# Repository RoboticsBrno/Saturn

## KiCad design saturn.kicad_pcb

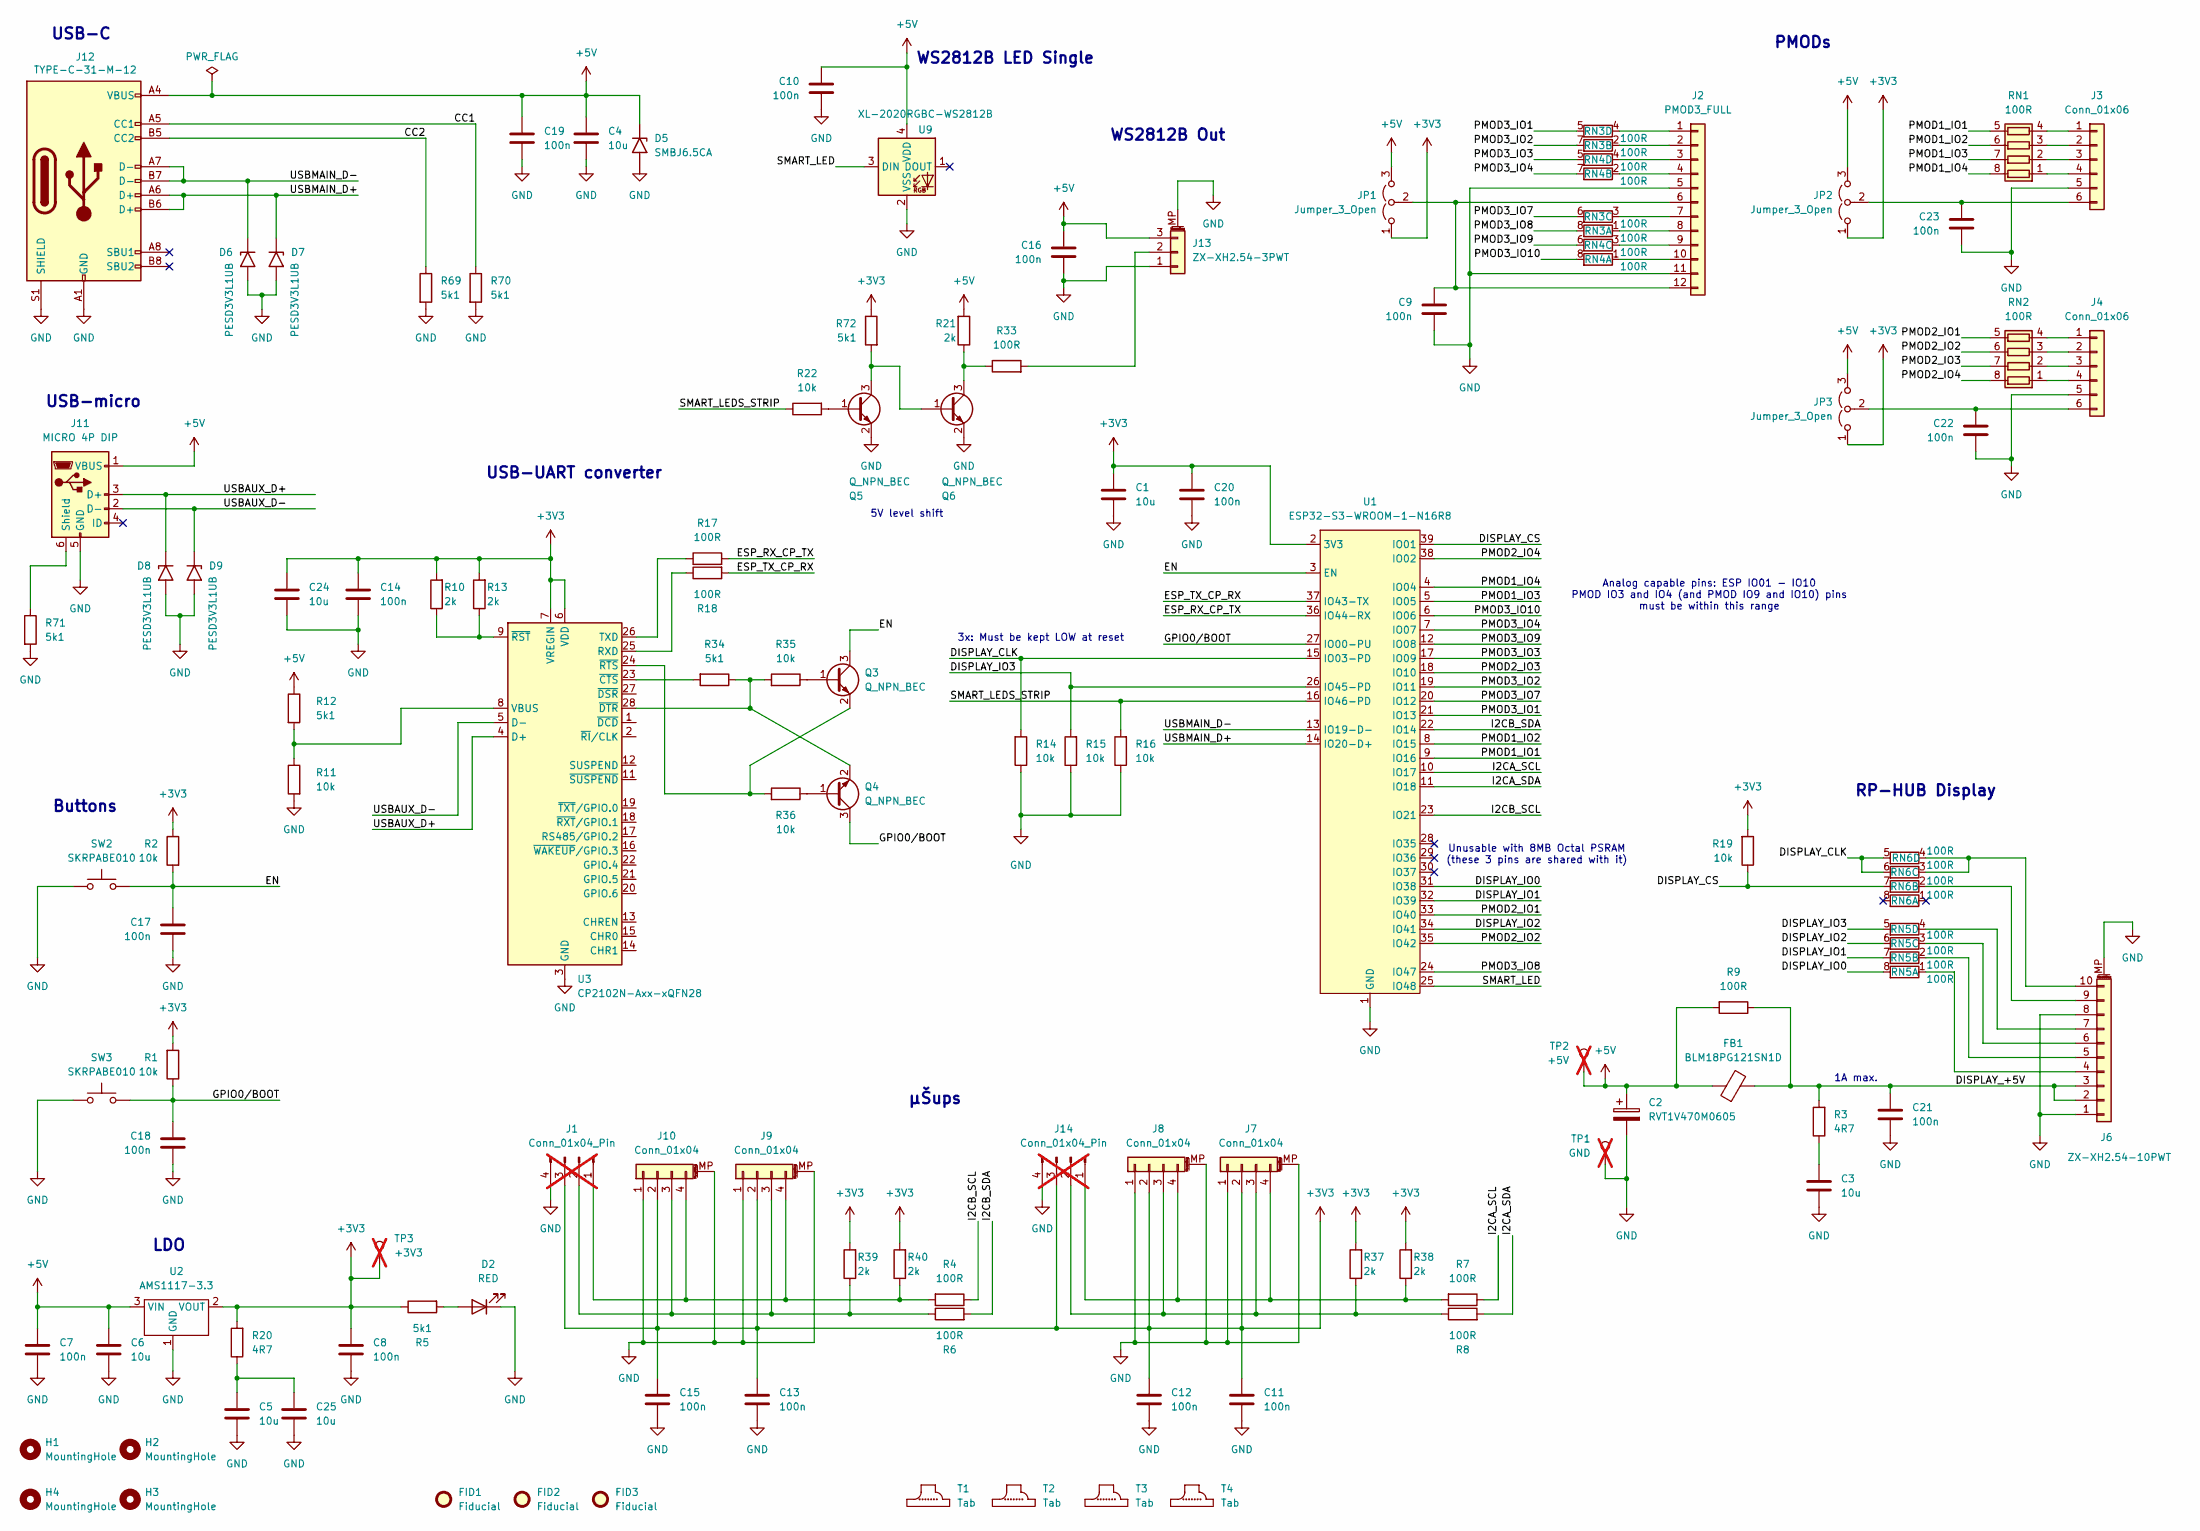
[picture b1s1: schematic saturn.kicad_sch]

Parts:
C1, C3, C4, C5, C6, C24, C25: 10u; C_0805_2012Metric; LCSC C15850
C2: RVT1V470M0605; CP_Elec_6.3x5.4; LCSC C72522
C7, C8, C9, C10, C11, C12, C13, C14, C15, C16, C17, C18, C19, C20, C21, C22, C23: 100n; C_0402_1005Metric; LCSC C307331
D2: RED; LED_0603_1608Metric; LCSC C965799
D5: SMBJ6.5CA; D_SMB; LCSC C7420377
D6, D7, D8, D9: PESD3V3L1UB; D_SOD-523; LCSC C3001945
FB1: BLM18PG121SN1D; L_0603_1608Metric; LCSC C14709
FID1, FID2, FID3: Fiducial; Fiducial_1mm_Mask2mm
H1, H2, H3, H4: MountingHole; MountingHole_3.2mm_M3_DIN965
J1, J14: Conn_01x04_Pin; PinSocket_1x04_P2.54mm_Vertical; not fitted
J2: PMOD3_FULL; PinSocket_PMOD_full; LCSC C2897426
J3, J4: Conn_01x06; PinSocket_PMOD_Half; LCSC C2897388
J6: ZX-XH2.54-10PWT; JST-XH-SMD-10Pin; LCSC C7429679
J7, J8, J9, J10: Conn_01x04; JST_SH_SM04B-SRSS-TB_1x04-1MP_P1.00mm_Horizontal; LCSC C7430446
J11: MICRO 4P DIP; USB_MICRO 4P DIP; LCSC C456008
J12: TYPE-C-31-M-12; USB_C_Receptacle_HRO_TYPE-C-31-M-12_With_THR_Paste; LCSC C165948
J13: ZX-XH2.54-3PWT; JST-XH-SMD-3Pin; LCSC C7429672
JP1, JP2, JP3: Jumper_3_Open; PinHeader_1x03_P2.54mm_Vertical_SMD_Pin1Left_LargePads; LCSC C41417360
Q3, Q4, Q5, Q6: Q_NPN_BEC; SOT-23; LCSC C20526
R1, R2, R11, R14, R15, R16, R19, R22, R35, R36: 10k; R_0402_1005Metric; LCSC C25744
R3, R20: 4R7; R_0805_2012Metric; LCSC C17675
R4, R6, R7, R8, R9, R17, R18, R33: 100R; R_0402_1005Metric; LCSC C25076
R5, R12, R34, R69, R70, R71, R72: 5k1; R_0402_1005Metric; LCSC C25905
R10, R13, R21, R37, R38, R39, R40: 2k; R_0402_1005Metric; LCSC C4109
RN1, RN2, RN3, RN4, RN5, RN6: 100R; R_Array_Convex_4x0603; LCSC C25506
SW2, SW3: SKRPABE010; SW_SMD_LargePads; LCSC C115360
T1, T2, T3, T4: Tab
TP1: GND; PinHeader_1x01_P2.54mm_Vertical; not fitted
TP2: +5V; PinHeader_1x01_P2.54mm_Vertical; not fitted
TP3: +3V3; PinHeader_1x01_P2.54mm_Vertical; not fitted
U1: ESP32-S3-WROOM-1-N16R8; ESP32-S3-WROOM; LCSC C2913202
U2: AMS1117-3.3; SOT-223-3_TabPin2; LCSC C6186
U3: CP2102N-Axx-xQFN28; QFN-28-1EP_5x5mm_P0.5mm_EP3.35x3.35mm; LCSC C964632
U9: XL-2020RGBC-WS2812B; LED_WS2812B-2020_PLCC4_2.0x2.0mm; LCSC C5349955

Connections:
+3V3: C1.1, C8.1, C11.1, C12.1, C13.1, C14.1, C15.1, C20.1, C24.1, J1.3, J7.2, J8.2, J9.2, J10.2, J14.3, JP1.1 (A), JP2.1 (A), JP3.1 (A), R1.2, R2.1, R5.1, R10.2, R13.2, R19.2, R20.2, R37.2, R38.2, R39.2, R40.2, R72.1, TP3.1 (1_1), U1.2 (3V3), U2.2 (VOUT), U3.6 (VDD), U3.7 (VREGIN)
+5V: C2.1, C4.1, C6.1, C7.1, C10.1, C16.1, C19.1, D5.1 (A1), FB1.1, J11.1 (VBUS), J12.A4 (VBUS), J12.A9 (VBUS), J12.B4 (VBUS), J12.B9 (VBUS), J13.3, JP1.3 (B), JP2.3 (B), JP3.3 (B), R9.2, R12.1, R21.2, TP2.1 (1_1), U2.3 (VIN), U9.4 (VDD)
/CC1: J12.A5 (CC1), R70.1
/CC2: J12.B5 (CC2), R69.1
/DISPLAY_+5V: C21.1, FB1.2, J6.2, J6.3, R3.2, R9.1
/DISPLAY_CLK: R14.2, RN6.5 (R4.2), RN6.6 (R3.2), U1.15 (IO03-PD)
/DISPLAY_CS: R19.1, RN6.7 (R2.2), U1.39 (IO01)
/DISPLAY_IO0: RN5.8 (R1.2), U1.31 (IO38)
/DISPLAY_IO1: RN5.7 (R2.2), U1.32 (IO39)
/DISPLAY_IO2: RN5.6 (R3.2), U1.34 (IO41)
/DISPLAY_IO3: R15.2, RN5.5 (R4.2), U1.26 (IO45-PD)
/EN: C17.1, Q3.3 (C), R2.2, SW2.1, U1.3 (EN)
/ESP_RX_CP_TX: R17.2, U1.36 (IO44-RX)
/ESP_TX_CP_RX: R18.2, U1.37 (IO43-TX)
/GPIO0/BOOT: C18.1, Q4.3 (C), R1.1, SW3.1, U1.27 (IO00-PU)
/I2CA_SCL: R7.1, U1.10 (IO17)
/I2CA_SDA: R8.2, U1.11 (IO18)
/I2CB_SCL: R4.1, U1.23 (IO21)
/I2CB_SDA: R6.2, U1.22 (IO14)
/PMOD1_IO1: RN1.5 (R4.2), U1.9 (IO16)
/PMOD1_IO2: RN1.6 (R3.2), U1.8 (IO15)
/PMOD1_IO3: RN1.7 (R2.2), U1.5 (IO05)
/PMOD1_IO4: RN1.8 (R1.2), U1.4 (IO04)
/PMOD2_IO1: RN2.5 (R4.2), U1.33 (IO40)
/PMOD2_IO2: RN2.6 (R3.2), U1.35 (IO42)
/PMOD2_IO3: RN2.7 (R2.2), U1.18 (IO10)
/PMOD2_IO4: RN2.8 (R1.2), U1.38 (IO02)
/PMOD3_IO1: RN3.5 (R4.2), U1.21 (IO13)
/PMOD3_IO2: RN3.7 (R2.2), U1.19 (IO11)
/PMOD3_IO3: RN4.5 (R4.2), U1.17 (IO09)
/PMOD3_IO4: RN4.7 (R2.2), U1.7 (IO07)
/PMOD3_IO7: RN3.6 (R3.2), U1.20 (IO12)
/PMOD3_IO8: RN3.8 (R1.2), U1.24 (IO47)
/PMOD3_IO9: RN4.6 (R3.2), U1.12 (IO08)
/PMOD3_IO10: RN4.8 (R1.2), U1.6 (IO06)
/SMART_LED: U1.25 (IO48), U9.3 (DIN)
/SMART_LEDS_STRIP: R16.2, R22.1, U1.16 (IO46-PD)
/USBAUX_D+: D8.1 (A1), J11.3 (D+), U3.4 (D+)
/USBAUX_D-: D9.1 (A1), J11.2 (D-), U3.5 (D-)
/USBMAIN_D+: D7.1 (A1), J12.A6 (D+), J12.B6 (D+), U1.14 (IO20-D+)
/USBMAIN_D-: D6.1 (A1), J12.A7 (D-), J12.B7 (D-), U1.13 (IO19-D-)
GND: C1.2, C2.2, C3.2, C4.2, C5.2, C6.2, C7.2, C8.2, C9.2, C10.2, C11.2, C12.2, C13.2, C14.2, C15.2, C16.2, C17.2, C18.2, C19.2, C20.2, C21.2, C22.2, C23.2, C24.2, C25.2, D2.1 (K), D5.2 (A2), D6.2 (A2), D7.2 (A2), D8.2 (A2), D9.2 (A2), J1.4, J2.5, J2.11, J3.5, J4.5, J6.1, J6.8, J6.MP (MountPin), J7.1, J7.MP (MountPin), J8.1, J8.MP (MountPin), J9.1, J9.MP (MountPin), J10.1, J10.MP (MountPin), J11.5 (GND), J12.A1 (GND), J12.A12 (GND), J12.B1 (GND), J12.B12 (GND), J12.S1 (SHIELD), J13.1, J13.MP (MountPin), J14.4, Q5.2 (E), Q6.2 (E), R11.2, R14.1, R15.1, R16.1, R69.2, R70.2, R71.2, SW2.2, SW3.2, TP1.1 (1_1), U1.1 (GND), U1.40 (GND), U1.41 (GND), U2.1 (GND), U3.3 (GND), U3.29 (GND), U9.2 (VSS)
unnamed: C3.1, R3.1
unnamed: C5.1, C25.1, R20.1
unnamed: D2.2 (A), R5.2
unnamed: J1.1, J9.4, J10.4, R4.2, R40.1
unnamed: J1.2, J9.3, J10.3, R6.1, R39.1
unnamed: J2.1, RN3.4 (R4.1)
unnamed: J2.2, RN3.2 (R2.1)
unnamed: J2.3, RN4.4 (R4.1)
unnamed: J2.4, RN4.2 (R2.1)
unnamed: J2.7, RN3.3 (R3.1)
unnamed: J2.8, RN3.1 (R1.1)
unnamed: J2.9, RN4.3 (R3.1)
unnamed: J2.10, RN4.1 (R1.1)
unnamed: C9.1, J2.6, J2.12, JP1.2 (C)
unnamed: J3.1, RN1.4 (R4.1)
unnamed: J3.2, RN1.3 (R3.1)
unnamed: J3.3, RN1.2 (R2.1)
unnamed: J3.4, RN1.1 (R1.1)
unnamed: C23.1, J3.6, JP2.2 (C)
unnamed: J4.1, RN2.4 (R4.1)
unnamed: J4.2, RN2.3 (R3.1)
unnamed: J4.3, RN2.2 (R2.1)
unnamed: J4.4, RN2.1 (R1.1)
unnamed: C22.1, J4.6, JP3.2 (C)
unnamed: J6.4, RN5.1 (R1.1)
unnamed: J6.5, RN5.2 (R2.1)
unnamed: J6.6, RN5.3 (R3.1)
unnamed: J6.7, RN5.4 (R4.1)
unnamed: J6.9, RN6.2 (R2.1)
unnamed: J6.10, RN6.3 (R3.1), RN6.4 (R4.1)
unnamed: J11.6 (Shield), R71.1
unnamed: J13.2, R33.2
unnamed: J7.4, J8.4, J14.1, R7.2, R38.1
unnamed: J7.3, J8.3, J14.2, R8.1, R37.1
unnamed: Q3.1 (B), R35.1
unnamed: Q3.2 (E), R36.2, U3.24 (~RTS)
unnamed: Q4.1 (B), R36.1
unnamed: Q4.2 (E), R34.1, R35.2, U3.28 (~DTR)
unnamed: Q5.1 (B), R22.2
unnamed: Q5.3 (C), Q6.1 (B), R72.2
unnamed: Q6.3 (C), R21.1, R33.1
unnamed: R18.1, U3.25 (RXD)
unnamed: R17.1, U3.26 (TXD)
unnamed: R11.1, R12.2, U3.8 (VBUS)
unnamed: R34.2, U3.23 (~CTS)
unnamed: R10.1, R13.1, U3.9 (~RST)

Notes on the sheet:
USB-UART converter
Unusable with 8MB Octal PSRAM (these 3 pins are shared with it)
WS2812B LED Single
3x: Must be kept LOW at reset
1A max.
RP-HUB Display
µŠups
PMODs
USB-micro
WS2812B Out
USB-C
LDO
5V level shift
Buttons
Analog capable pins: ESP IO01 - IO10 PMOD IO3 and IO4 (and PMOD IO9 and IO10) pins must be within this range

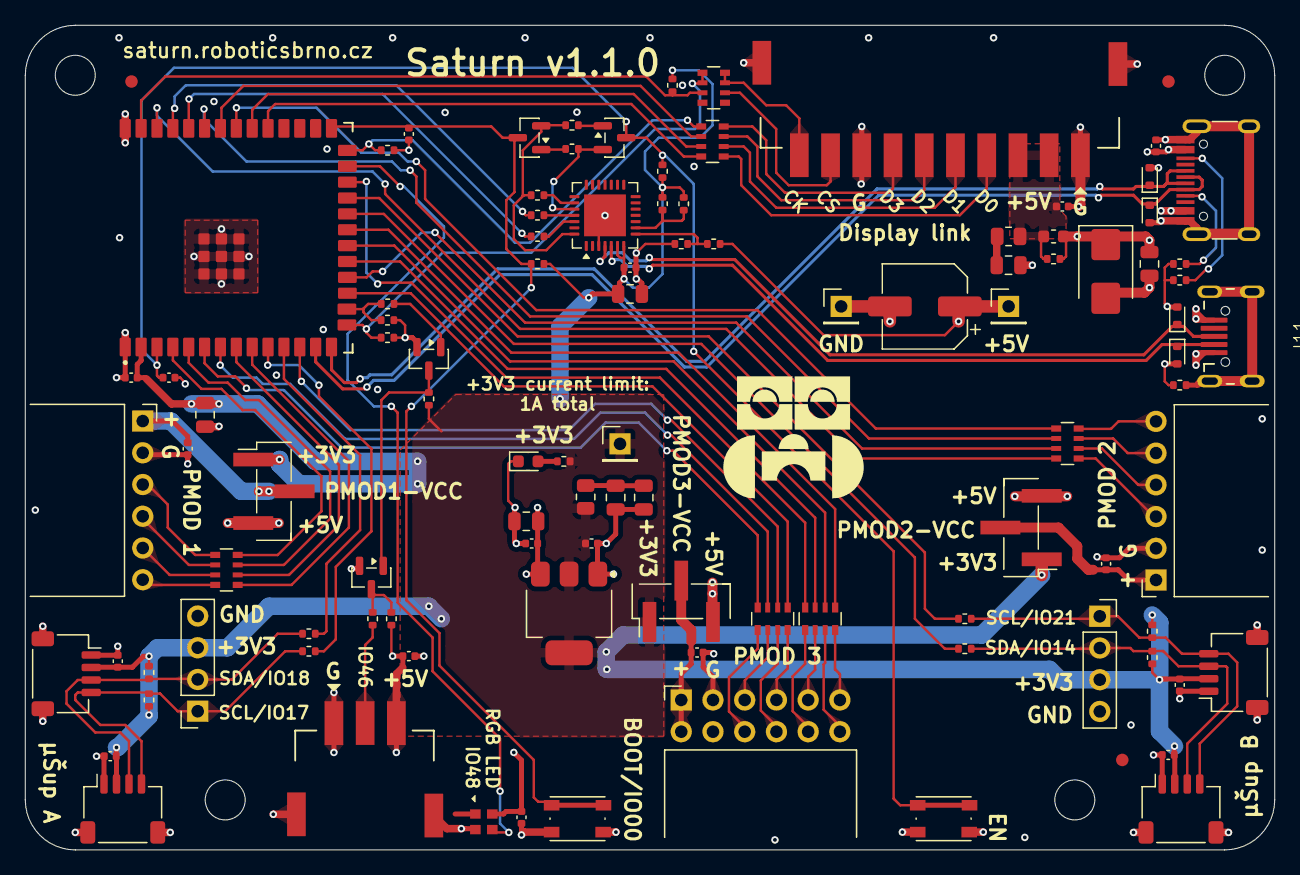
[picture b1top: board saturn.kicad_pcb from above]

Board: 4 copper layers, 100.0 x 66.0 mm, 112 parts (0 on the bottom side), 88 nets.

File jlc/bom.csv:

Comment,Designator,Footprint,LCSC
100R,"R4,R6,R7,R8,R9,R17,R18,R33",Resistor_SMD:R_0402_1005Metric,C25076
ZX-XH2.54-3PWT,J13,JST-XH-SMT:JST-XH-SMD-3Pin,C7429672
2k,"R10,R13,R21,R37,R38,R39,R40",Resistor_SMD:R_0402_1005Metric,C4109
Jumper_3_Open,"JP1,JP2,JP3",PinHeader_jumper:PinHeader_1x03_P2.54mm_Vertical_SMD_Pin1Left_LargePads,C41417360
5k1,"R5,R12,R34,R69,R70,R71,R72",Resistor_SMD:R_0402_1005Metric,C25905
10k,"R1,R2,R11,R14,R15,R16,R19,R22,R35,R36",Resistor_SMD:R_0402_1005Metric,C25744
100n,"C7,C8,C9,C10,C11,C12,C13,C14,C15,C16,C17,C18,C19,C20,C21,C22,C23",Capacitor_SMD:C_0402_1005Metric,C307331
100R,"RN1,RN2,RN3,RN4,RN5,RN6",Resistor_SMD:R_Array_Convex_4x0603,C25506
10u,"C1,C3,C4,C5,C6,C24,C25",Capacitor_SMD:C_0805_2012Metric,C15850
MICRO 4P DIP,J11,USB_Conn:USB_MICRO 4P DIP,C456008
Q_NPN_BEC,"Q3,Q4,Q5,Q6",Package_TO_SOT_SMD:SOT-23,C20526
4R7,"R3,R20",Resistor_SMD:R_0805_2012Metric,C17675
SMBJ6.5CA,D5,Diode_SMD:D_SMB,C7420377
Conn_01x04,"J7,J8,J9,J10",Connector_JST:JST_SH_SM04B-SRSS-TB_1x04-1MP_P1.00mm_Horizontal,C7430446
SKRPABE010,"SW2,SW3",Switch_SMT:SW_SMD_LargePads,C115360
PESD3V3L1UB,"D6,D7,D8,D9",Diode_SMD:D_SOD-523,C3001945
RED,D2,LED_SMD:LED_0603_1608Metric,C965799
BLM18PG121SN1D,FB1,Inductor_SMD:L_0603_1608Metric,C14709
XL-2020RGBC-WS2812B,U9,XL-2020RGBC-WS2812B:LED_WS2812B-2020_PLCC4_2.0x2.0mm,C5349955
ZX-XH2.54-10PWT,J6,JST-XH-SMT:JST-XH-SMD-10Pin,C7429679
CP2102N-Axx-xQFN28,U3,Package_DFN_QFN:QFN-28-1EP_5x5mm_P0.5mm_EP3.35x3.35mm,C964632
ESP32-S3-WROOM-1-N16R8,U1,ESP32-WROOM:ESP32-S3-WROOM,C2913202
AMS1117-3.3,U2,Package_TO_SOT_SMD:SOT-223-3_TabPin2,C6186
Conn_01x06,"J3,J4",PinSocket_PMOD:PinSocket_PMOD_Half,C2897388
TYPE-C-31-M-12,J12,USB_Conn:USB_C_Receptacle_HRO_TYPE-C-31-M-12_With_THR_Paste,C165948
PMOD3_FULL,J2,PinSocket_PMOD:PinSocket_PMOD_full,C2897426
RVT1V470M0605,C2,Capacitor_SMD:CP_Elec_6.3x5.4,C72522

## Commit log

2026-02-27 Add hw review 2nd version
2026-03-03 Release v1.0.0
2026-04-11 Switch to Kicad 10
2026-04-23 Fix PMOD ADC pin assignment, tune silkscreen
2026-04-25 Add PMOD polarity mark on Top
2026-04-25 Fix 5V unroute
2026-04-25 Use unipolar TVS diodes, tune switch values
2026-04-25 Use SMT PMOD jumper header
2026-04-25 Use SMT JST-XH connectors
2026-04-25 Remove unneeded JST XH files
2026-04-25 Add CHANGELOG.md
2026-04-25 Tune silkscreen
2026-05-10 Tune silkscreen, enlarge SMT switch pads
2026-05-10 Add project-specific ESP32, USB, WS2812B footprints
2026-05-10 Add enlarge-pad switch footprint
2026-05-10 Add fp-lib-table
2026-05-10 Add fubar Button 3D model
2026-05-13 Use 0805 10u capacitors (cheaper)
2026-05-13 Use AMS1117-3.3 LDO (cheaper)
2026-05-13 Add LDO output cap series resistance
2026-05-16 Separate LED Strip to IO46 with level shift, tune layout
2026-05-17 Add panelization and fab Makefile
2026-05-17 Add kik.json
2026-05-17 Tune layout, POS corrections, kik.json
2026-05-17 Ignore -bridged-wtf-DRC-thing-, tune Makefile
2026-05-17 Replace Micro-USB connector
2026-05-17 Release v1.1.0
